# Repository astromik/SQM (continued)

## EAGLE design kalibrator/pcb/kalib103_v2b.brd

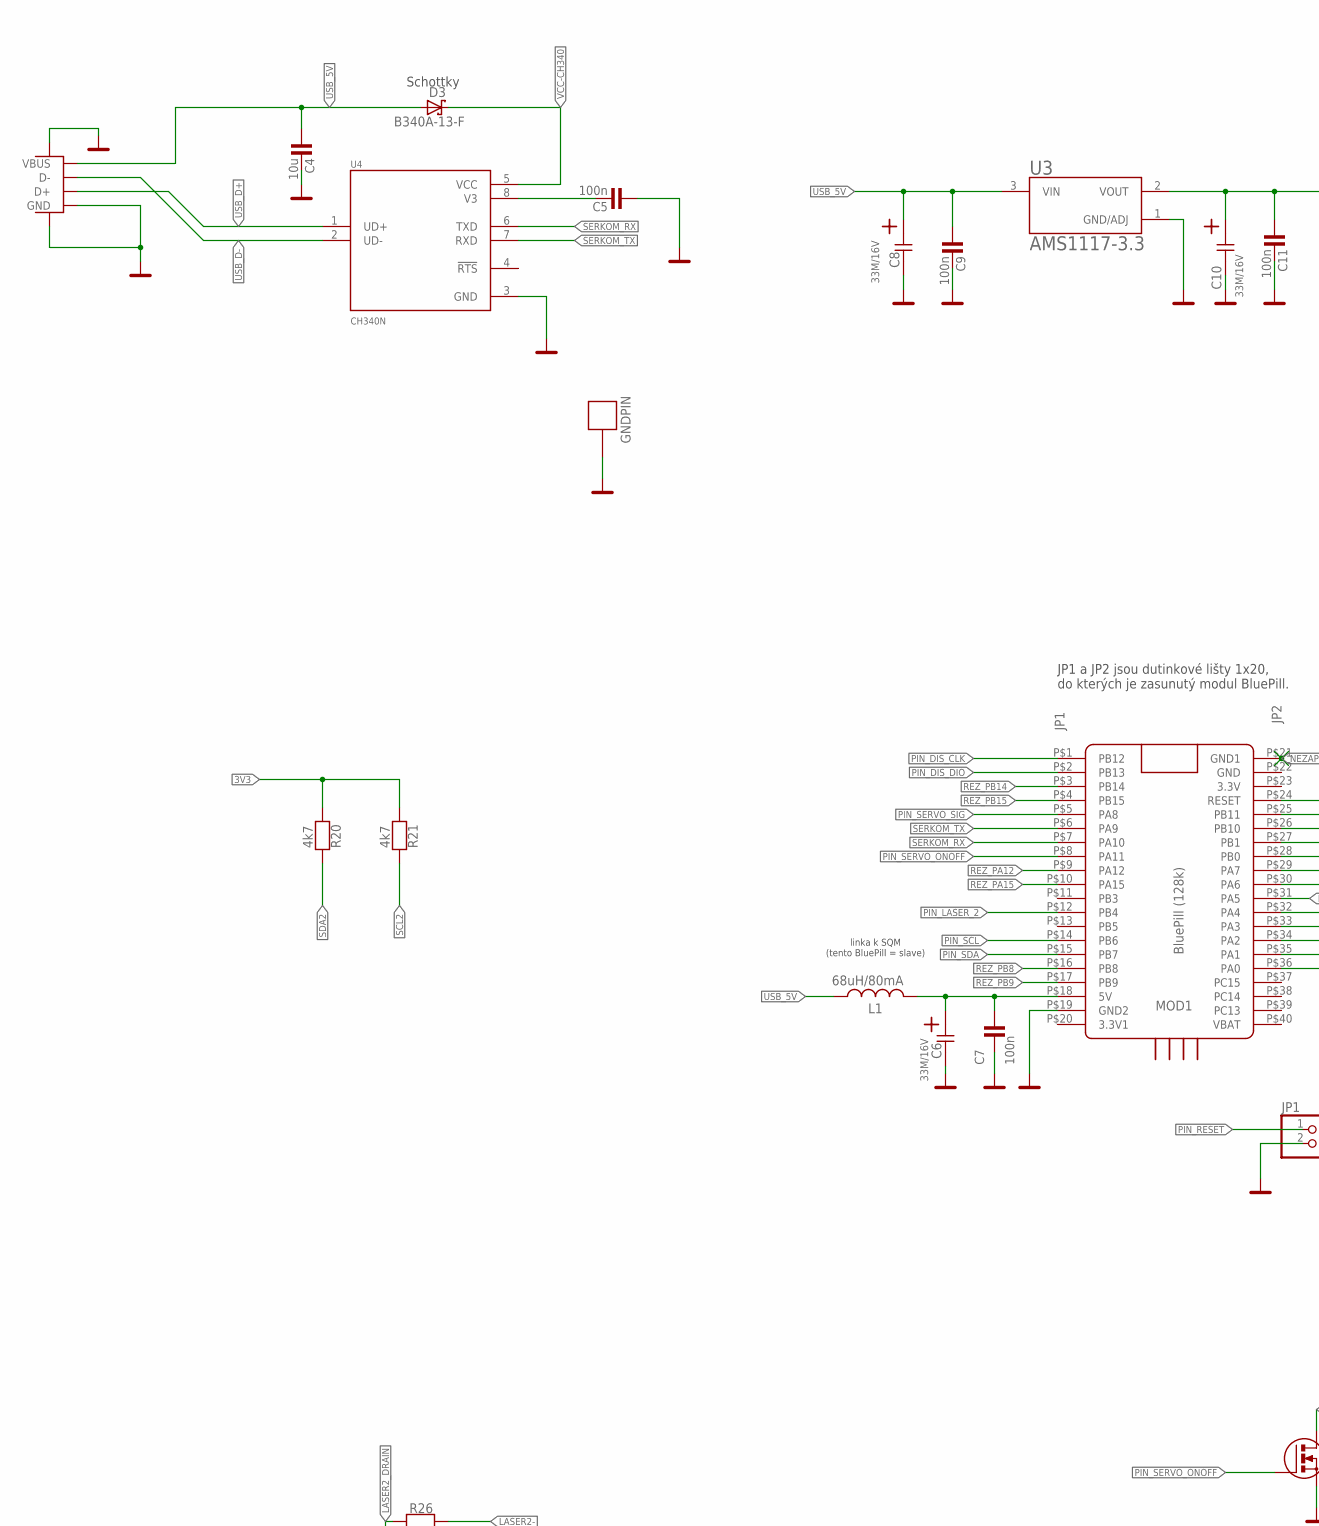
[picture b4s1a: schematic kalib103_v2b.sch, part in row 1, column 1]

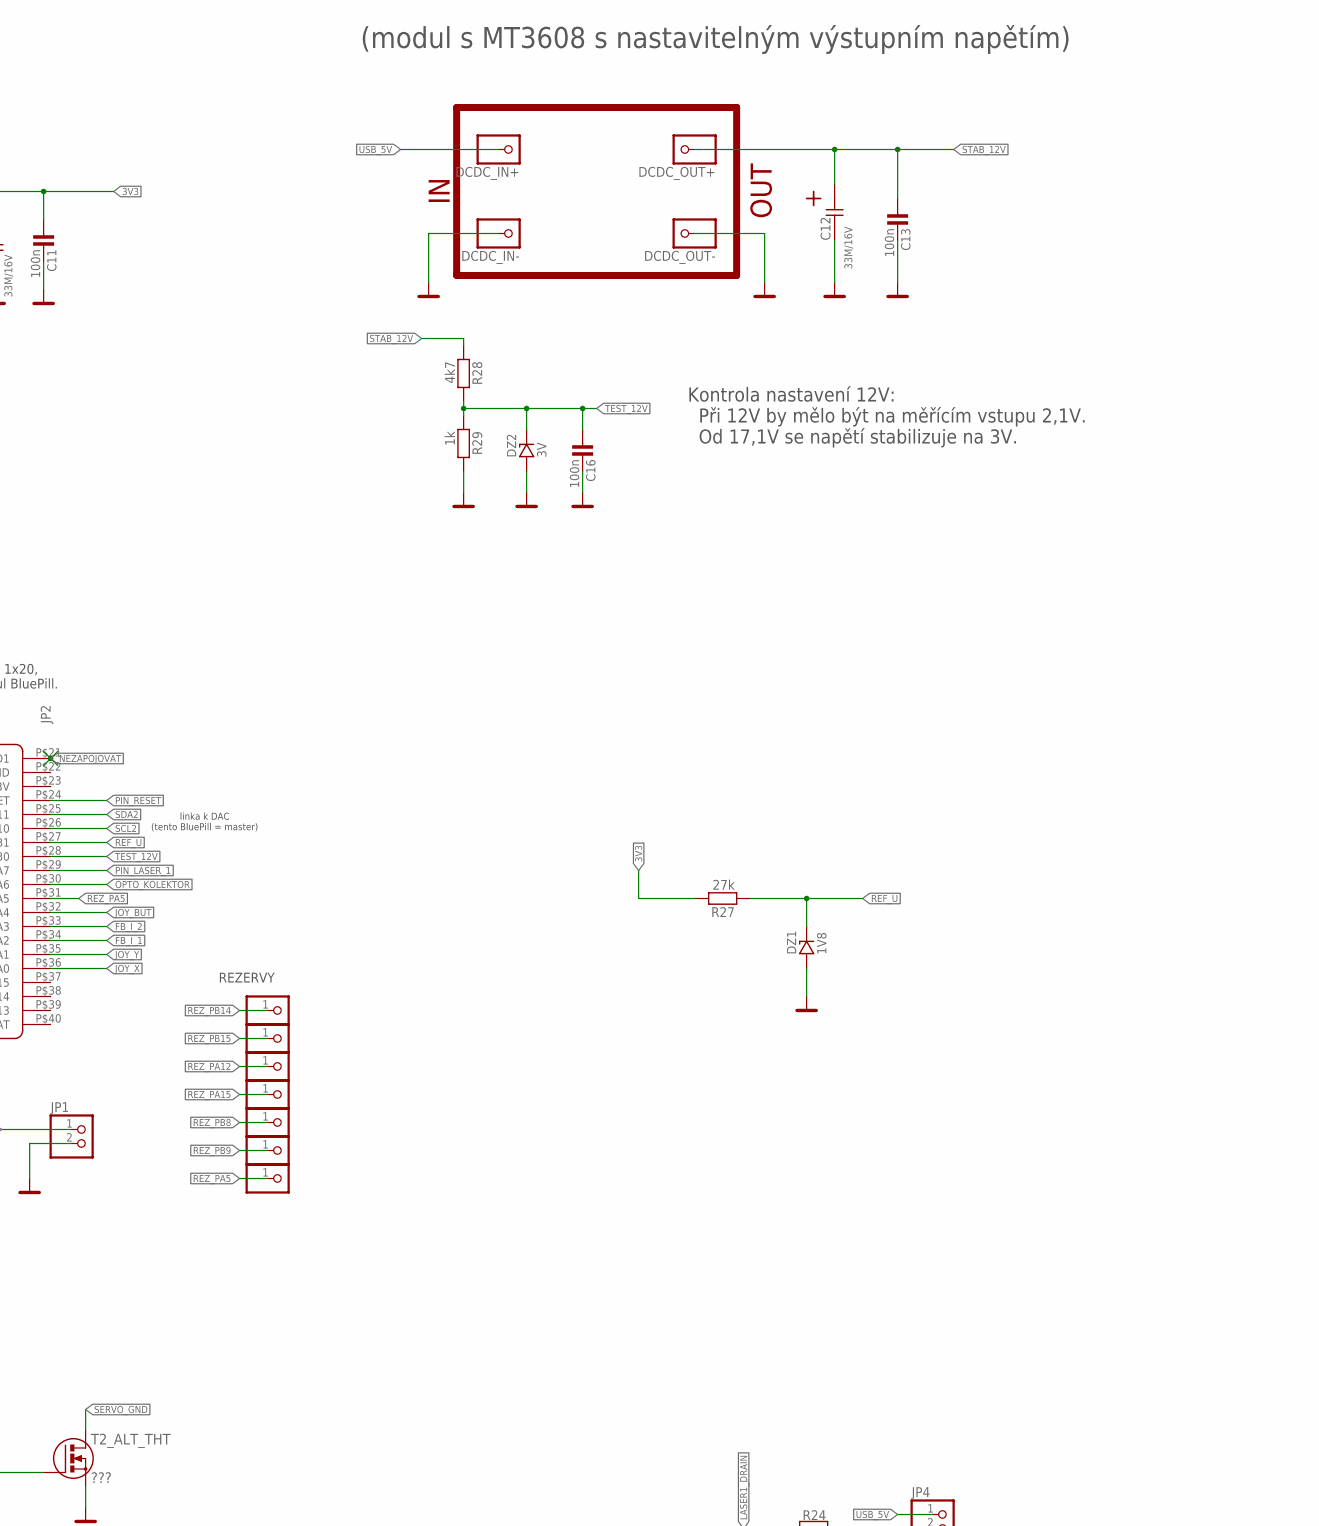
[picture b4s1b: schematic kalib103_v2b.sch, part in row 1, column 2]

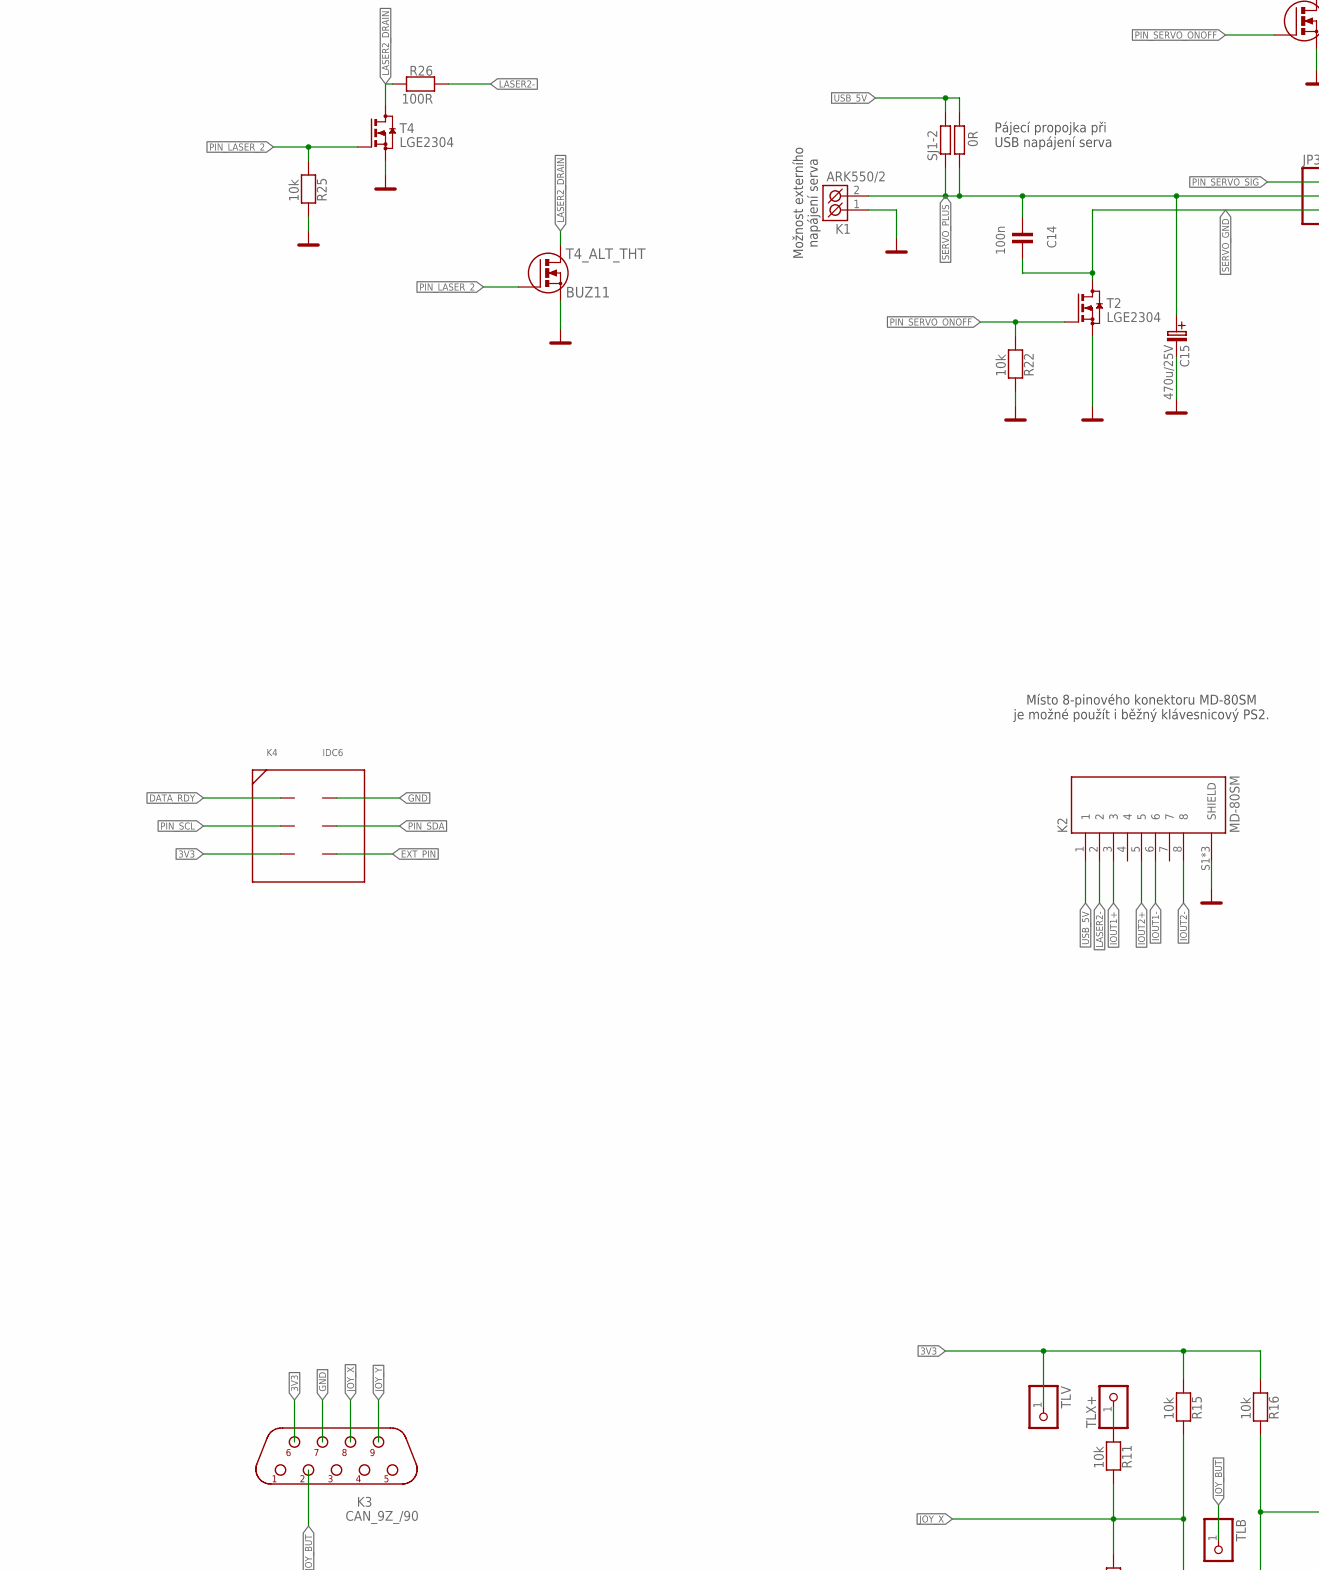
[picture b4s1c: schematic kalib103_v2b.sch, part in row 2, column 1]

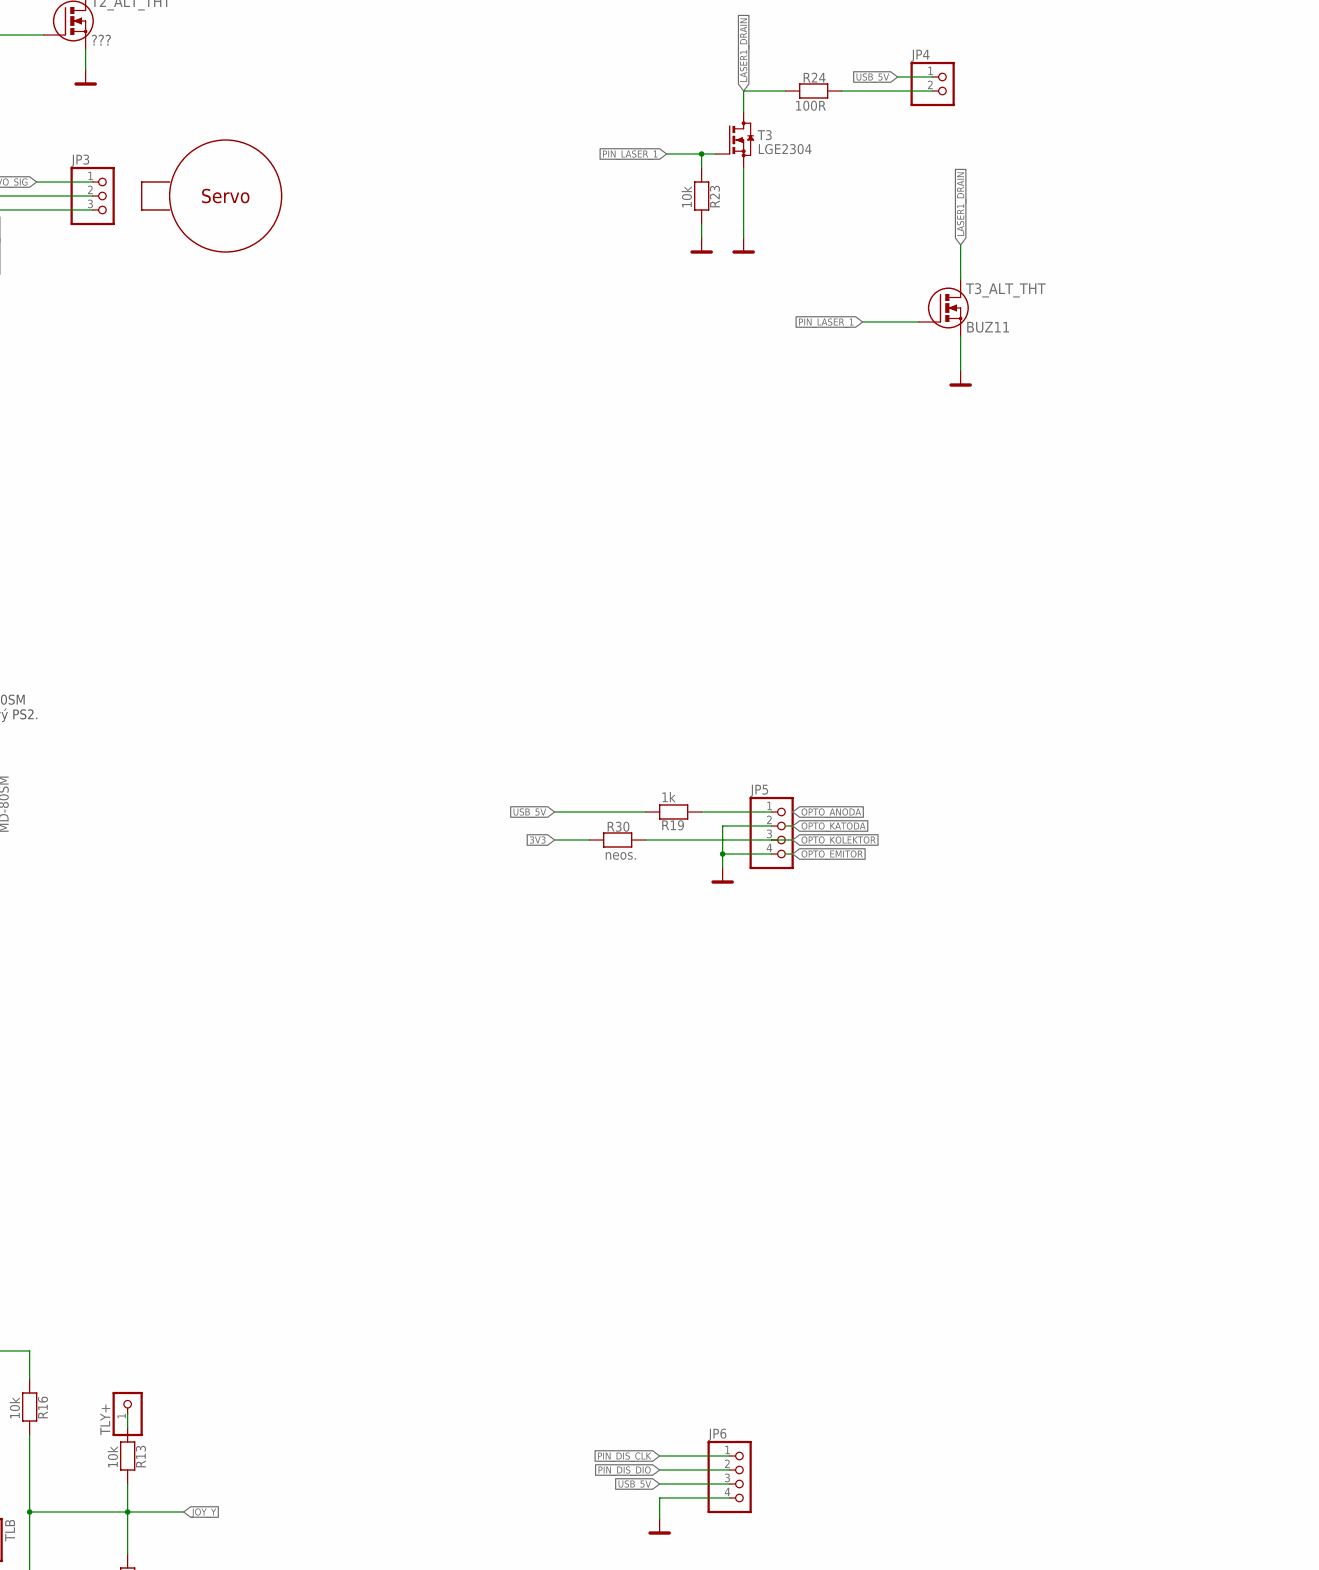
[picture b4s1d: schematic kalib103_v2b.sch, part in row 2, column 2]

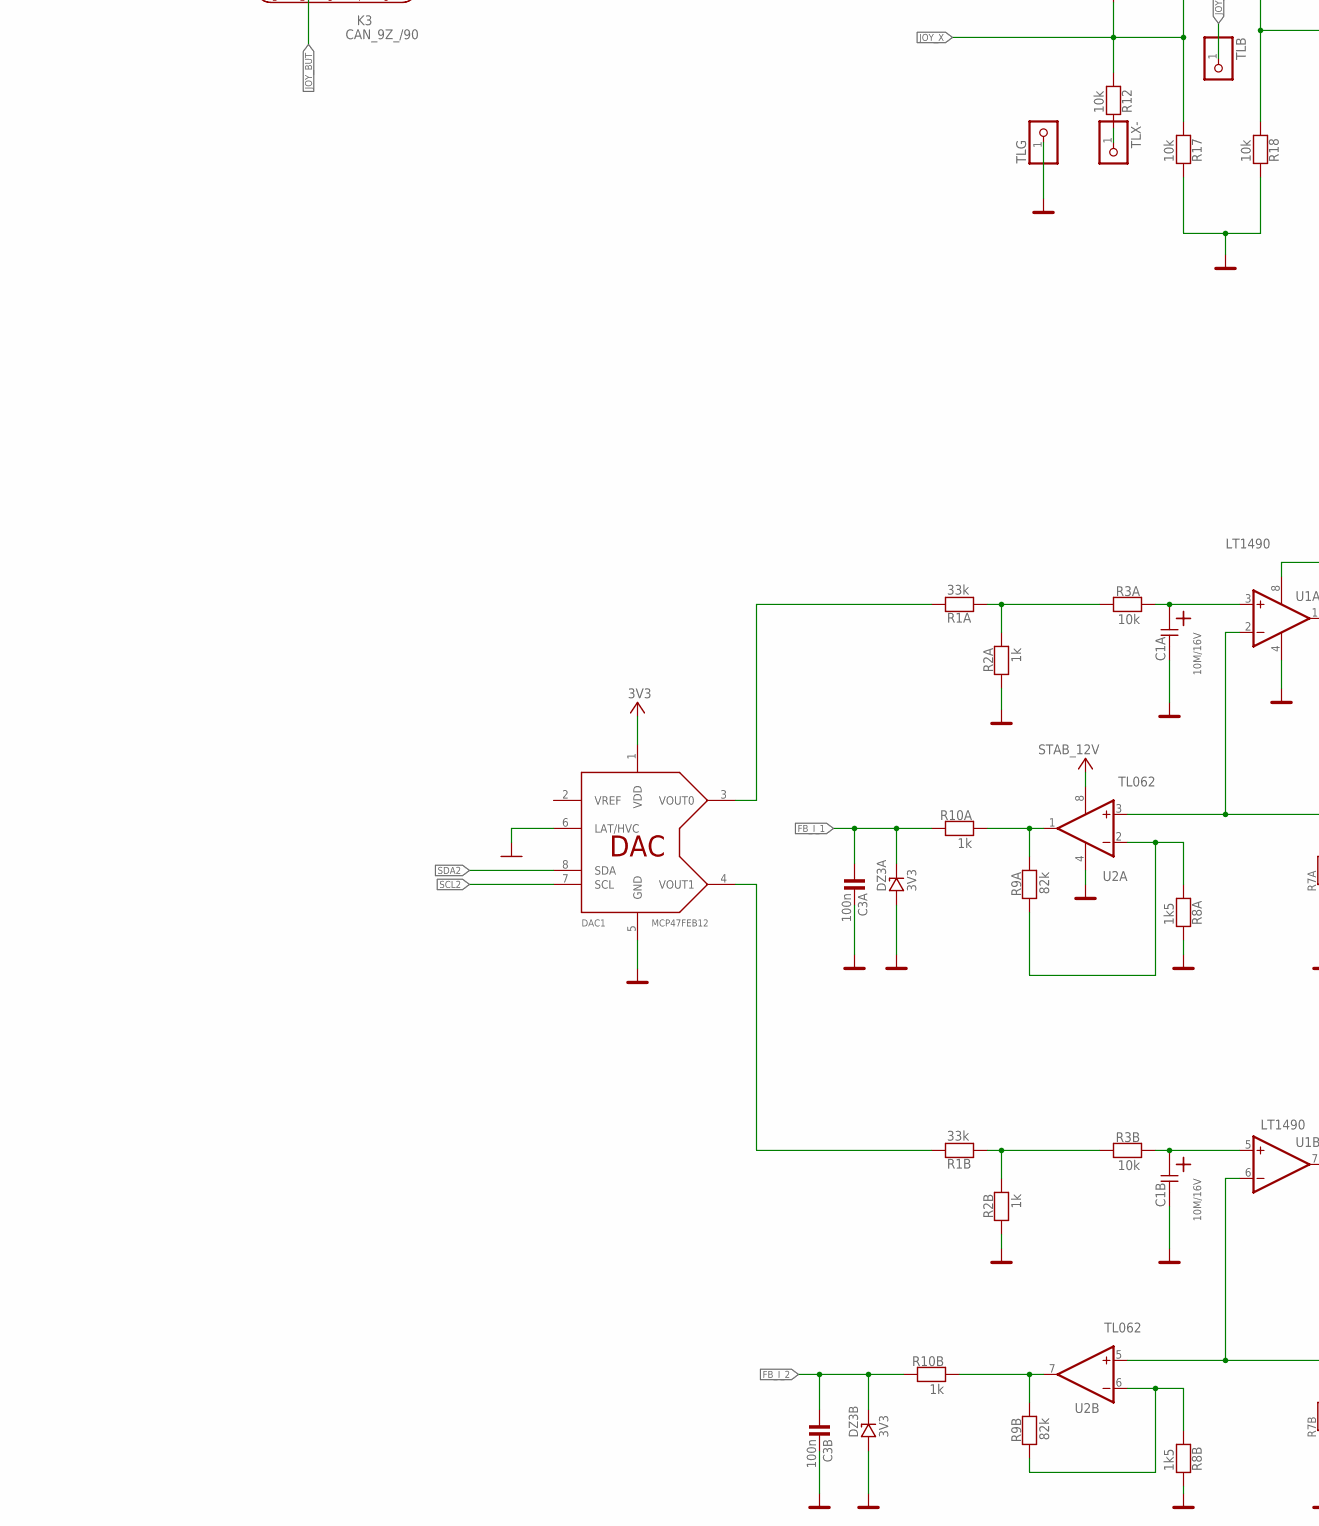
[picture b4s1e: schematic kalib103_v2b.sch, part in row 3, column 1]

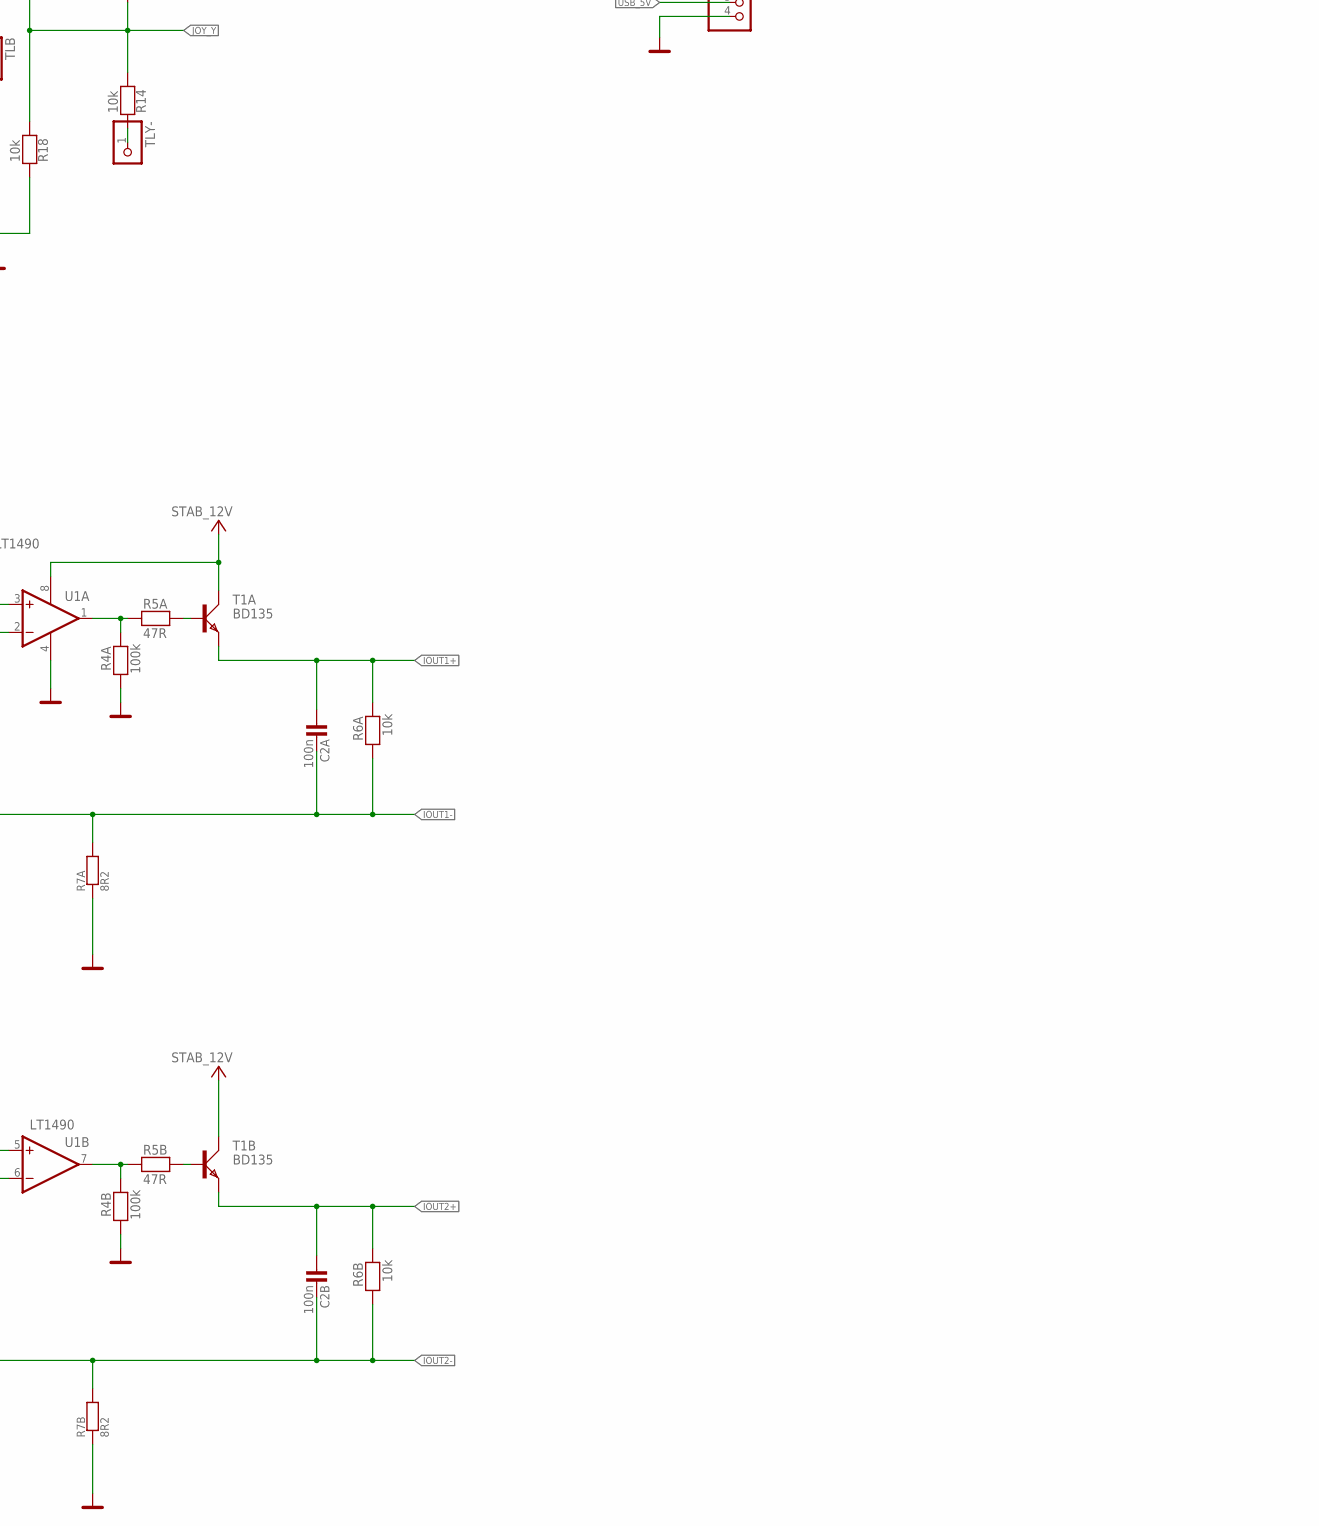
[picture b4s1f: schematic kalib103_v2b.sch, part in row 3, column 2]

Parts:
C1A, C1B: 10M/16V; 6032
C2A, C2B, C3A, C3B, C5, C7, C9, C11, C13, C14, C16: 100n; 0805
C4: 10u; 0805
C6, C8, C10, C12: 33M/16V; 6032
C15: 470u/25V; C-EL_5
D3: B340A-13-F; SMB
DAC1: MCP47FEB12; TSSOP-8
DCDC_IN+: pin; 1X1-BIGPOGO
DCDC_IN-: pin; 1X1-BIGPOGO
DCDC_OUT+: pin; 1X1-BIGPOGO
DCDC_OUT-: pin; 1X1-BIGPOGO
DZ1: 1V8; SOD-80
DZ2: 3V; SOD-80
DZ3A, DZ3B: 3V3; SOD-80
GNDPIN: BIGPIN
JP1, JP4: PINHD-1X2; 1X02
JP3: PINHD-1X3; 1X03
JP5, JP6: PINHD-1X4; 1X04
K1: ARK550/2
K2: MD-80SM; CUI_MD-80SM
K3: CAN_9Z_/90; CAN9Z/90
K4: IDC6
K5: USBPTH; USB-B-PTH
L1: 68uH/80mA; L0805
MOD1: BluePill (128k); BLUE_PILL
R1A, R1B: 33k; 0805
R2A, R2B, R10A, R10B, R19, R29: 1k; 0805
R3A, R3B, R6A, R6B, R11, R12, R13, R14, R15, R16, R17, R18, R22, R23, R25: 10k; 0805
R4A, R4B: 100k; 0805
R5A, R5B: 47R; 0805
R7A, R7B: 8R2; R-12,7
R8A, R8B: 1k5; 0805
R9A, R9B: 82k; 0805
R20, R21, R28: 4k7; 0805
R24, R26: 100R; 0805
R27: 27k; 0805
R30: neos.; 0805
REZERVA1, REZERVA2, REZERVA3, REZERVA4, REZERVA5, REZERVA6, REZERVA7: PINHD-1X1; 1X01
SJ1-1, SJ1-2: 0R; R0603
T1A, T1B: BD135; TO126AS
T2, T3, T4: LGE2304; SOT23
T2_ALT_THT: ???; TO-220S
T3_ALT_THT, T4_ALT_THT: BUZ11; TO-220S
TLB: PINHD-1X1; 1X01
TLG: PINHD-1X1; 1X01
TLV: PINHD-1X1; 1X01
TLX+: PINHD-1X1; 1X01
TLX-: PINHD-1X1; 1X01
TLY+: PINHD-1X1; 1X01
TLY-: PINHD-1X1; 1X01
U1: LT1490; SOP-8
U2: TL062; SOP-8
U3: AMS1117-3.3; SOT229P700X180-4N
U4: CH340N; SOIC127P600X160-8N
U$1: SERVO_MG_996

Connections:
3V3: C10.1, C11.1, DAC1.1 (VDD), K3.6, K4.P5 (PIN5), R15.2, R16.2, R20.2, R21.2, R27.2, R30.2, TLV.1, U3.2 (VOUT)
BOD_TLX+: R11.2, TLX+.1
BOD_TLX-: R12.1, TLX-.1
BOD_TLY+: R13.2, TLY+.1
BOD_TLY-: R14.1, TLY-.1
B_T1_A: R5A.2, T1A.B
B_T1_B: R5B.2, T1B.B
CH340-V3: C5.2, U4.8 (V3)
DAC_OUT_0: DAC1.3 (VOUT0), R1A.1
DAC_OUT_1: DAC1.4 (VOUT1), R1B.1
DATA_RDY: K4.P1 (PIN1)
EXT_PIN: K4.P6 (PIN6)
FB_I_1: C3A.1, DZ3A.K, MOD1.P$34 (PA2), R10A.2
FB_I_2: C3B.1, DZ3B.K, MOD1.P$33 (PA3), R10B.2
GND: C1A.2, C1B.2, C3A.2, C3B.2, C4.2, C5.1, C6.2, C7.1, C8.2, C9.2, C10.2, C11.2, C12.2, C13.2, C15.C- (C_EL-), C16.2, DAC1.5 (GND), DAC1.6 (LAT/HVC), DCDC_IN-.P$1, DCDC_OUT-.P$1, DZ1.A, DZ2.A, DZ3A.A, DZ3B.A, GNDPIN.P$1, JP1.2, JP5.2, JP5.4, JP6.4, K1.1 (K1), K2.S1 (SHIELD), K2.S2 (SHIELD), K2.S3 (SHIELD), K3.7, K4.P2 (PIN2), K5.GND, K5.P$2 (SHIELD), K5.SHIELD (SHIELD2), MOD1.P$19 (GND2), R2A.2, R2B.2, R4A.2, R4B.2, R7A.1, R7B.1, R8A.1, R8B.1, R17.1, R18.1, R22.1, R23.1, R25.1, R29.2, T2.2 (S), T2_ALT_THT.3 (S), T3.2 (S), T3_ALT_THT.3 (S), T4.2 (S), T4_ALT_THT.3 (S), TLG.1, U1.4 (V-), U2.4 (V-), U3.1 (GND/ADJ), U4.3 (GND)
IN_DELIC_A: R1A.2, R2A.1, R3A.2
IN_DELIC_B: R1B.2, R2B.1, R3B.2
IOUT1+: C2A.1, K2.3, R6A.1, T1A.E
IOUT1-: C2A.2, K2.6, R6A.2, R7A.2, U1.2 (-IN), U2.3 (+IN)
IOUT2+: C2B.1, K2.5, R6B.1, T1B.E
IOUT2-: C2B.2, K2.8, R6B.2, R7B.2, U1.6 (-IN), U2.5 (+IN)
JOY_BUT: K3.2, MOD1.P$32 (PA4), TLB.1
JOY_X: K3.8, MOD1.P$36 (PA0), R11.1, R12.2, R15.1, R17.2
JOY_Y: K3.9, MOD1.P$35 (PA1), R13.1, R14.2, R16.1, R18.2
LASER1-: JP4.2, R24.1
LASER1_DRAIN: R24.2, T3.3 (D), T3_ALT_THT.2 (D)
LASER2-: K2.2, R26.1
LASER2_DRAIN: R26.2, T4.3 (D), T4_ALT_THT.2 (D)
NEZAPOJOVAT: MOD1.P$21 (GND1)
OPTO_ANODA: JP5.1, R19.2
OPTO_KOLEKTOR: JP5.3, MOD1.P$30 (PA6), R30.1
OUT_I1_FB: R9A.1, R10A.1, U2.1 (OUT)
OUT_I2_FB: R9B.1, R10B.1, U2.7 (OUT)
OUT_U1A: R4A.1, R5A.1, U1.1 (OUT)
OUT_U1B: R4B.1, R5B.1, U1.7 (OUT)
PIN_DIS_CLK: JP6.1, MOD1.P$1 (PB12)
PIN_DIS_DIO: JP6.2, MOD1.P$2 (PB13)
PIN_LASER_1: MOD1.P$29 (PA7), R23.2, T3.1 (G), T3_ALT_THT.1 (G)
PIN_LASER_2: MOD1.P$12 (PB4), R25.2, T4.1 (G), T4_ALT_THT.1 (G)
PIN_RESET: JP1.1, MOD1.P$24 (RESET)
PIN_SCL: K4.P3 (PIN3), MOD1.P$14 (PB6)
PIN_SDA: K4.P4 (PIN4), MOD1.P$15 (PB7)
PIN_SERVO_ONOFF: MOD1.P$8 (PA11), R22.2, T2.1 (G), T2_ALT_THT.1 (G)
PIN_SERVO_SIG: JP3.1, MOD1.P$5 (PA8)
REF_U: DZ1.K, MOD1.P$27 (PB1), R27.1
REZ_PA5: MOD1.P$31 (PA5), REZERVA7.1
REZ_PA12: MOD1.P$9 (PA12), REZERVA3.1
REZ_PA15: MOD1.P$10 (PA15), REZERVA4.1
REZ_PB8: MOD1.P$16 (PB8), REZERVA5.1
REZ_PB9: MOD1.P$17 (PB9), REZERVA6.1
REZ_PB14: MOD1.P$3 (PB14), REZERVA1.1
REZ_PB15: MOD1.P$4 (PB15), REZERVA2.1
SCL2: DAC1.7 (SCL), MOD1.P$26 (PB10), R21.1
SDA2: DAC1.8 (SDA), MOD1.P$25 (PB11), R20.1
SERKOM_RX: MOD1.P$7 (PA10), U4.6 (TXD)
SERKOM_TX: MOD1.P$6 (PA9), U4.7 (RXD)
SERVO_GND: C14.2, JP3.3, T2.3 (D), T2_ALT_THT.2 (D)
SERVO_PLUS: C14.1, C15.C+ (C_EL+), JP3.2, K1.2 (K2), SJ1-1.1, SJ1-2.1
STAB_12V: C12.1, C13.1, DCDC_OUT+.P$1, R28.1, T1A.C, T1B.C, U1.8 (V+), U2.8 (V+)
TEST_12V: C16.1, DZ2.K, MOD1.P$28 (PB0), R28.2, R29.1
U1A_NEINVERT: C1A.1, R3A.1, U1.3 (+IN)
U1B_NEINVERT: C1B.1, R3B.1, U1.5 (+IN)
U2A_INVERT: R8A.2, R9A.2, U2.2 (-IN)
U2B_INVERT: R8B.2, R9B.2, U2.6 (-IN)
USB_5V: C4.1, C8.1, C9.1, D3.A, DCDC_IN+.P$1, JP4.1, JP6.3, K2.1, K5.VBUS, L1.1, R19.1, SJ1-1.2, SJ1-2.2, U3.3 (VIN)
USB_5V_STM: C6.1, C7.2, L1.2, MOD1.P$18 (5V)
USB_D+: K5.D+, U4.1 (UD+)
USB_D-: K5.D-, U4.2 (UD-)
VCC-CH340: D3.C, U4.5 (VCC)

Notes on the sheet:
JP2
JP1
JP1 a JP2 jsou dutinkové lišty 1x20, do kterých je zasunutý modul BluePill.
Schottky
OUT
linka k SQM (tento BluePill = slave)
linka k DAC (tento BluePill = master)
REZERVY
(modul s MT3608 s nastavitelným výstupním napětím)
Kontrola nastavení 12V: Při 12V by mělo být na měřícím vstupu 2,1V. Od 17,1V se napětí stabilizuje na 3V.
Pájecí propojka při USB napájení serva
Možnost externího napájení serva
Místo 8-pinového konektoru MD-80SM je možné použít i běžný klávesnicový PS2.

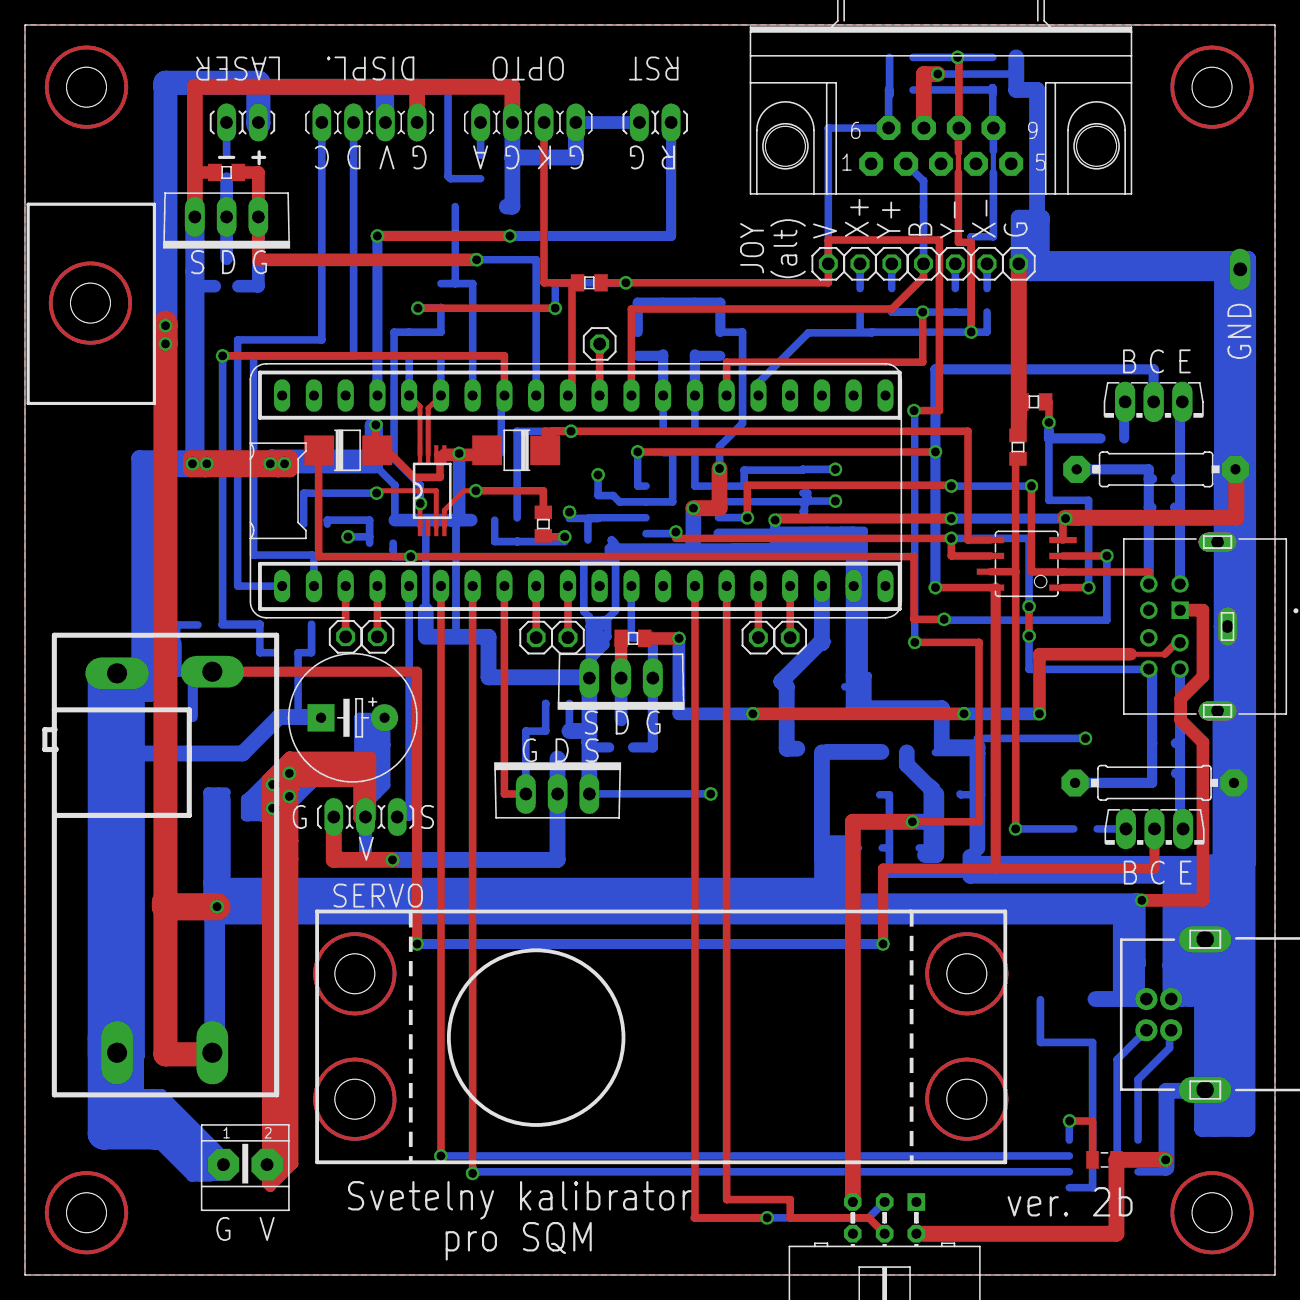
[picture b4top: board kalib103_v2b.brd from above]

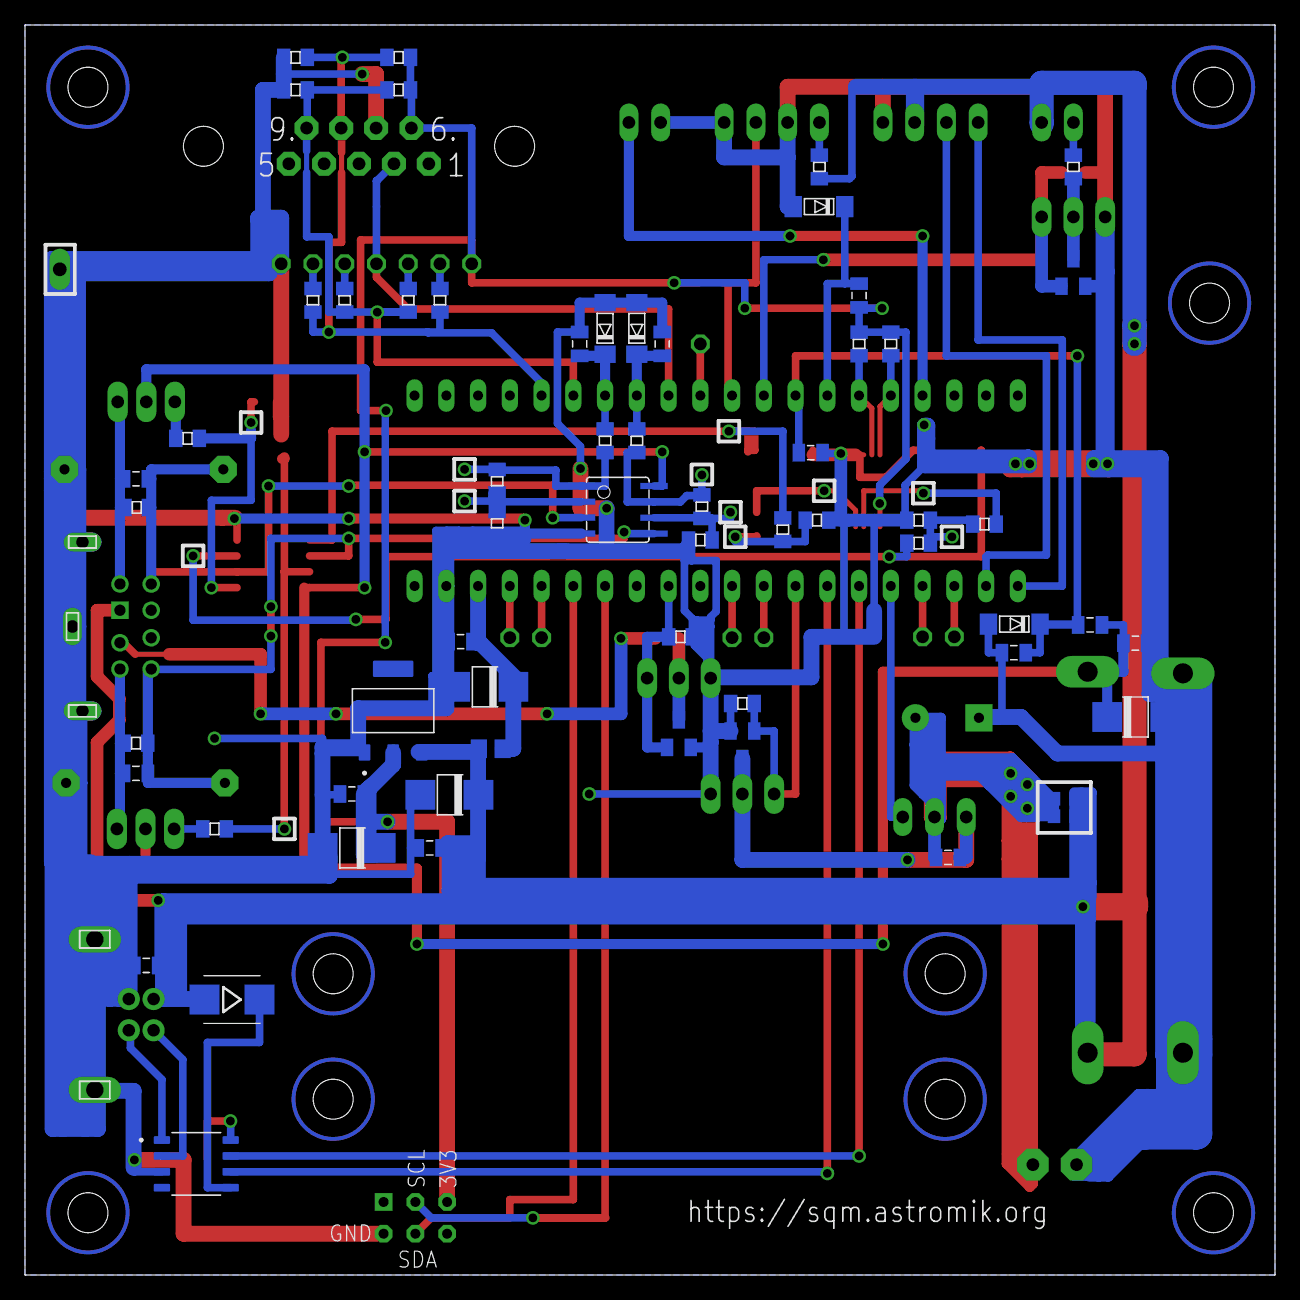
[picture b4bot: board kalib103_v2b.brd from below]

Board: 2 copper layers, 99.9 x 99.9 mm, 111 parts (61 on the bottom side), 66 nets.

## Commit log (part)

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2026-05-18 Initialize README with project details and images
    Added project description and images to README.
2026-05-18 Oprava nefunkční kalibrace
    Při pokusu o kalibraci světla se buňky, které nebyly obsaženy v kalibračním řetězci, mazaly (nastavovaly se na hodnoty 65535).
2026-05-19 Úpravy posledních verzí programů v návodech
    Změny verzí programů, překlepy, doplnění neprůměrovaných záznamů do trasovacího GPX souboru...
2026-05-21 Doplnění kalibračních tabulek
    Do složky "zbytky" doplněny zapomenuté kalibrační tabulky.
2026-05-22 Doplnění "HELP" souborů
    Doplnění balíku souborů s detailními nápovědami k funkcím na SD kartu do složky "\HELP"
2026-05-23 Doplnění README
    Doplnění funkcí do souboru README.
2026-05-23 Doplněn generátor výrobní dokumentace
    Podklady pro zprovoznění PHP generátoru výrobní dokumentace na jiném webovém serveru.
2026-05-24 Přesun části kódu do jiného repozitáře
    Části kódu pro kalibrátor (otočný podstavec pro měření směrových charakteristik SQM) byly přesunuty do zatím neveřejného repozitáře, protože ještě nejsou dodělané.
2026-05-24 Přesun složky HELP
    Složka HELP s detailními popisy funkcí, která má být umístěna na SD kartě byla v rámci repozitáře přesunuta z původní složky "programy\sd\" do složky "navody\sd\".
2026-05-24 Doplnění PDF verzí schémat
    Schémata pro SQM-BAS, SQM-DIS a SQM-GPS byla vyexportována z Eagle jako PDF soubory.
2026-05-24 Doplnění obrázků krabičky
    Podklady pro 3D tisk doplněny několika pohledy na jednotlivé části krabičky
2026-05-24 Úpravy v podkladech SQM-BAS
    Vyhozena složka s objednávkou u JLCPCB. Doplněn gerberovský ZIP.
2026-05-24 Úprava dat pro webový konfigurátor
    V datech byl nadbytečný ZIP, který obsahoval úplně to samé co už je v repozitáři. ZIP byl odstraněn.
2026-05-24 Doplněn soubor "tele_par.txt"
    Na SD kartu doplněn soubor "tele_par.txt" pro editaci parametrů dalekohledu. Návod k použití je v dokumentaci pro položku menu "DSO" (určování viditelnosti).
2026-06-12 Doplnění knihoven Adafruit
    Doplněny balíky knihoven:
    "Adafruit_sensor"
    "Adafruit_BusIO"
2026-06-13 Doplnění funkce "Astro Simulace"
    V menu "Astro" je možné zapnout položku "Simulace", která umožní astronomické výpočty pro zadané datum a čas. Tento datum a čas se zadává v menu "dAtuM", "CAS " a "ZonA". Při zapnuté simulaci nemá př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
2026-06-13 Doplnění BIN souborů pro STM32CubeProgrammer
    Poslední verze programu 2026-06-13 pro procesory STM32F401 a STM32F411, které je možné nahrát i bez Arduino IDE přímo do procesorové desky přes USB nebo STlink programem STM32CubeProgrammer.
2026-06-16 Simulace pro DSO, blikání menu, autokalibrace
    - Zavedení blikání položek "Datum", "Čas" a "Zóna" při zapnuté simulaci astro výpočtů jako signalizace, že se nastavená hodnota nezapisuje do RTC.
    - Stejně jako simulace planet je možné simulovat i DSO (týká se jen výpočtů elevace a azimutu).
    - Funkce autokalibrátoru se kompilují i ve veřejné verzi. Jejich zapnutí se ale provádí ručním zápisem hodnoty do EEPROM.
2026-06-16 Úpravy v problikávání signalizace simulace
    Při listování v menu se na položkách "Datum", "Čas" a "Zóna" při zapnuté simulaci vždycky nejdřív zobrazí normální název položky a až po 0,6 sekundách na chvíli (na 0,3 sekundy) blikne nápis "Si. on".
2026-06-16 Úpravy návodů pro funkce simulace
    Do návod k obsluze doplněny informace o problikávání menu "Datum", "Čas" a "Zóna" v režimu simulace astronomických výpočtů.
    Do návodu pro úpravy programu doplněn popis adresy 590 pro nastavení režimu kalibrátoru.
2026-06-16 Poslední verze BIN souborů
    BIN soubory pro verze 2026-06-16
